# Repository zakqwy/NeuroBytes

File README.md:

## NOTE
This repository is no longer actively maintained or current. This clean break helped us do many things, such as:
- switch microcontroller platforms from ATtiny88 (8-bit AVR) to STM32L0s (ARM Cortex M0+)
- move from a single-board-fits-all strategy to specific boards that represent different types of biological elements
- change signaling from a simple 200ms pulse to a flexible mesh networking protocol
The new repositories can be found under the NeuroTinker GitHub account, found here: https://github.com/neurotinker.
# NeuroBytes
Official repo for NeuroBytes, an open-source hardware neuron simulator created by NeuroTinker, LLC. An exhuastive history of the project can be found at https://hackaday.io/project/3339-neurobytes, while more information on the company and people behind the project can be found at https://www.neurotinker.com. A good source for up-to-date and interesting pictures are the various NeuroTinker social media accounts: https://www.instagram.com/neurotinker, https://www.twitter.com/neurotinker, and https://www.facebook.com/neurotinker.
## Background
NeuroBytes were created to bridge the gap between middle- and high-school biology classes and postsecondary neuroscience education. We believe that a hands-on, modular, free-form tool in the spirit of LEGO, littleBits, or SnapCircuits that uniquely focuses on core neuroscience principles can connect engineering and biology concepts and ultimately improve STEM/STEAM retention rates for students as they pursue higher education. Our company's history goes back to 2012 and work done independently by Andrew Salveson (an architect) and Joe Burdo (a neuroscientist). After Zach Fredin created the first few generations of hardware simulators in 2014, Joe and Zach found each other via Hackaday.io and decided to collaborate on the project. In 2016, we were awarded a Phase I SBIR grant from the National Science Foundation and continue to work full-time on the project. NeuroBytes are not yet available for commercial sale, but we have sold a number of prototype kits to educators and students at a wide variety of levels and are always interested in collaborations. The project's creators can be easily reached via email: joe[at]neurotinker[dot]com and zach[at]neurotinker[dot]com.
## Hardware
All hardware files can be found under the /HARDWARE folder in this repository. The NeuroBytes boards, currently in version 0.91, were designed in KiCad v4.x. Various custom schematic symbols and PCB footprints were used, which are included in ZF.lib. The board outline itself along with the copper layer NeuroTinker logo were modified and redied for KiCad use using Inkscape and Gimp; various files titled v091-logo.xxx and v091_outline.xxx are included in the repo and were used in this process. Note that the NeuroTinker logo is a registered trademark of NeuroTinker, LLC and cannot be used without explicit permission from the company. Having said that, we urge interested parties to build and commercially sell electronic neuron simulators and accessories based on the NeuroBytes platform, keeping in mind the requirements outlined under our chosen license (GPLv3).

## Firmware
All firmware files can be found under the /FIRMWARE folder in this repository. NeuroBytes (at least v0.91) are based around the ATtiny88 platform and programmed in AVR-C using the avrdude/gcc toolchain and an Adafruit USBtinyISP programmer. Each runtime program is standalone in its folder, including a suitable Makefile that configures the proper microcontroller fuses. As expected, the test_LED program just lights the RGB LED white to test a few connections; the v091_run-iaf (stands for "integrate-and-fire") folder holds the latest firmware iteration, and includes an operating mode for direct servo control (hold the 'mode' switch down for a few seconds to change this). As with any pre-commercial work-in-progress, the firmware will be changing rapidly but any code in this repo has been thoroughly tested (so let us know if it doesn't work).

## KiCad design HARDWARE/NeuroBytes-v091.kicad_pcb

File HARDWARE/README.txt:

Copyright 2016 by Zach Fredin, NeuroTinker LLC
5/15/2016

NeuroBytes v0.9 is the ninth hardware iteration of the NeuroBytes project, a product designed and manufactured by NeuroTinker, LLC. The project is released under the terms of the GNU General Public License version 3 (LICENSE.txt). These boards are still to be considered prototypes, and as such may have bugs and mistakes that have not yet been recognized or fixed.

Changes vs NeuroBytes v0.8:

- Added on-board potentiometer
- Both axon signals now route to hardware PWM-capable pins
- Added on-board LDO and associated capacitors
- Added Schottky diode on microcontroller voltage rail
- Added OSHW logo to silkscreen
- Reduced LED hole size slightly
- Added pogo pads for testing axons, dendrites, etc.
- Changed MODE switch to standard type (vs right-angle)
- General silkscreen improvements/simplifications

Note that the PCB design file includes three copies of the board, along with a pogo rig breakout and a few accessory boards.

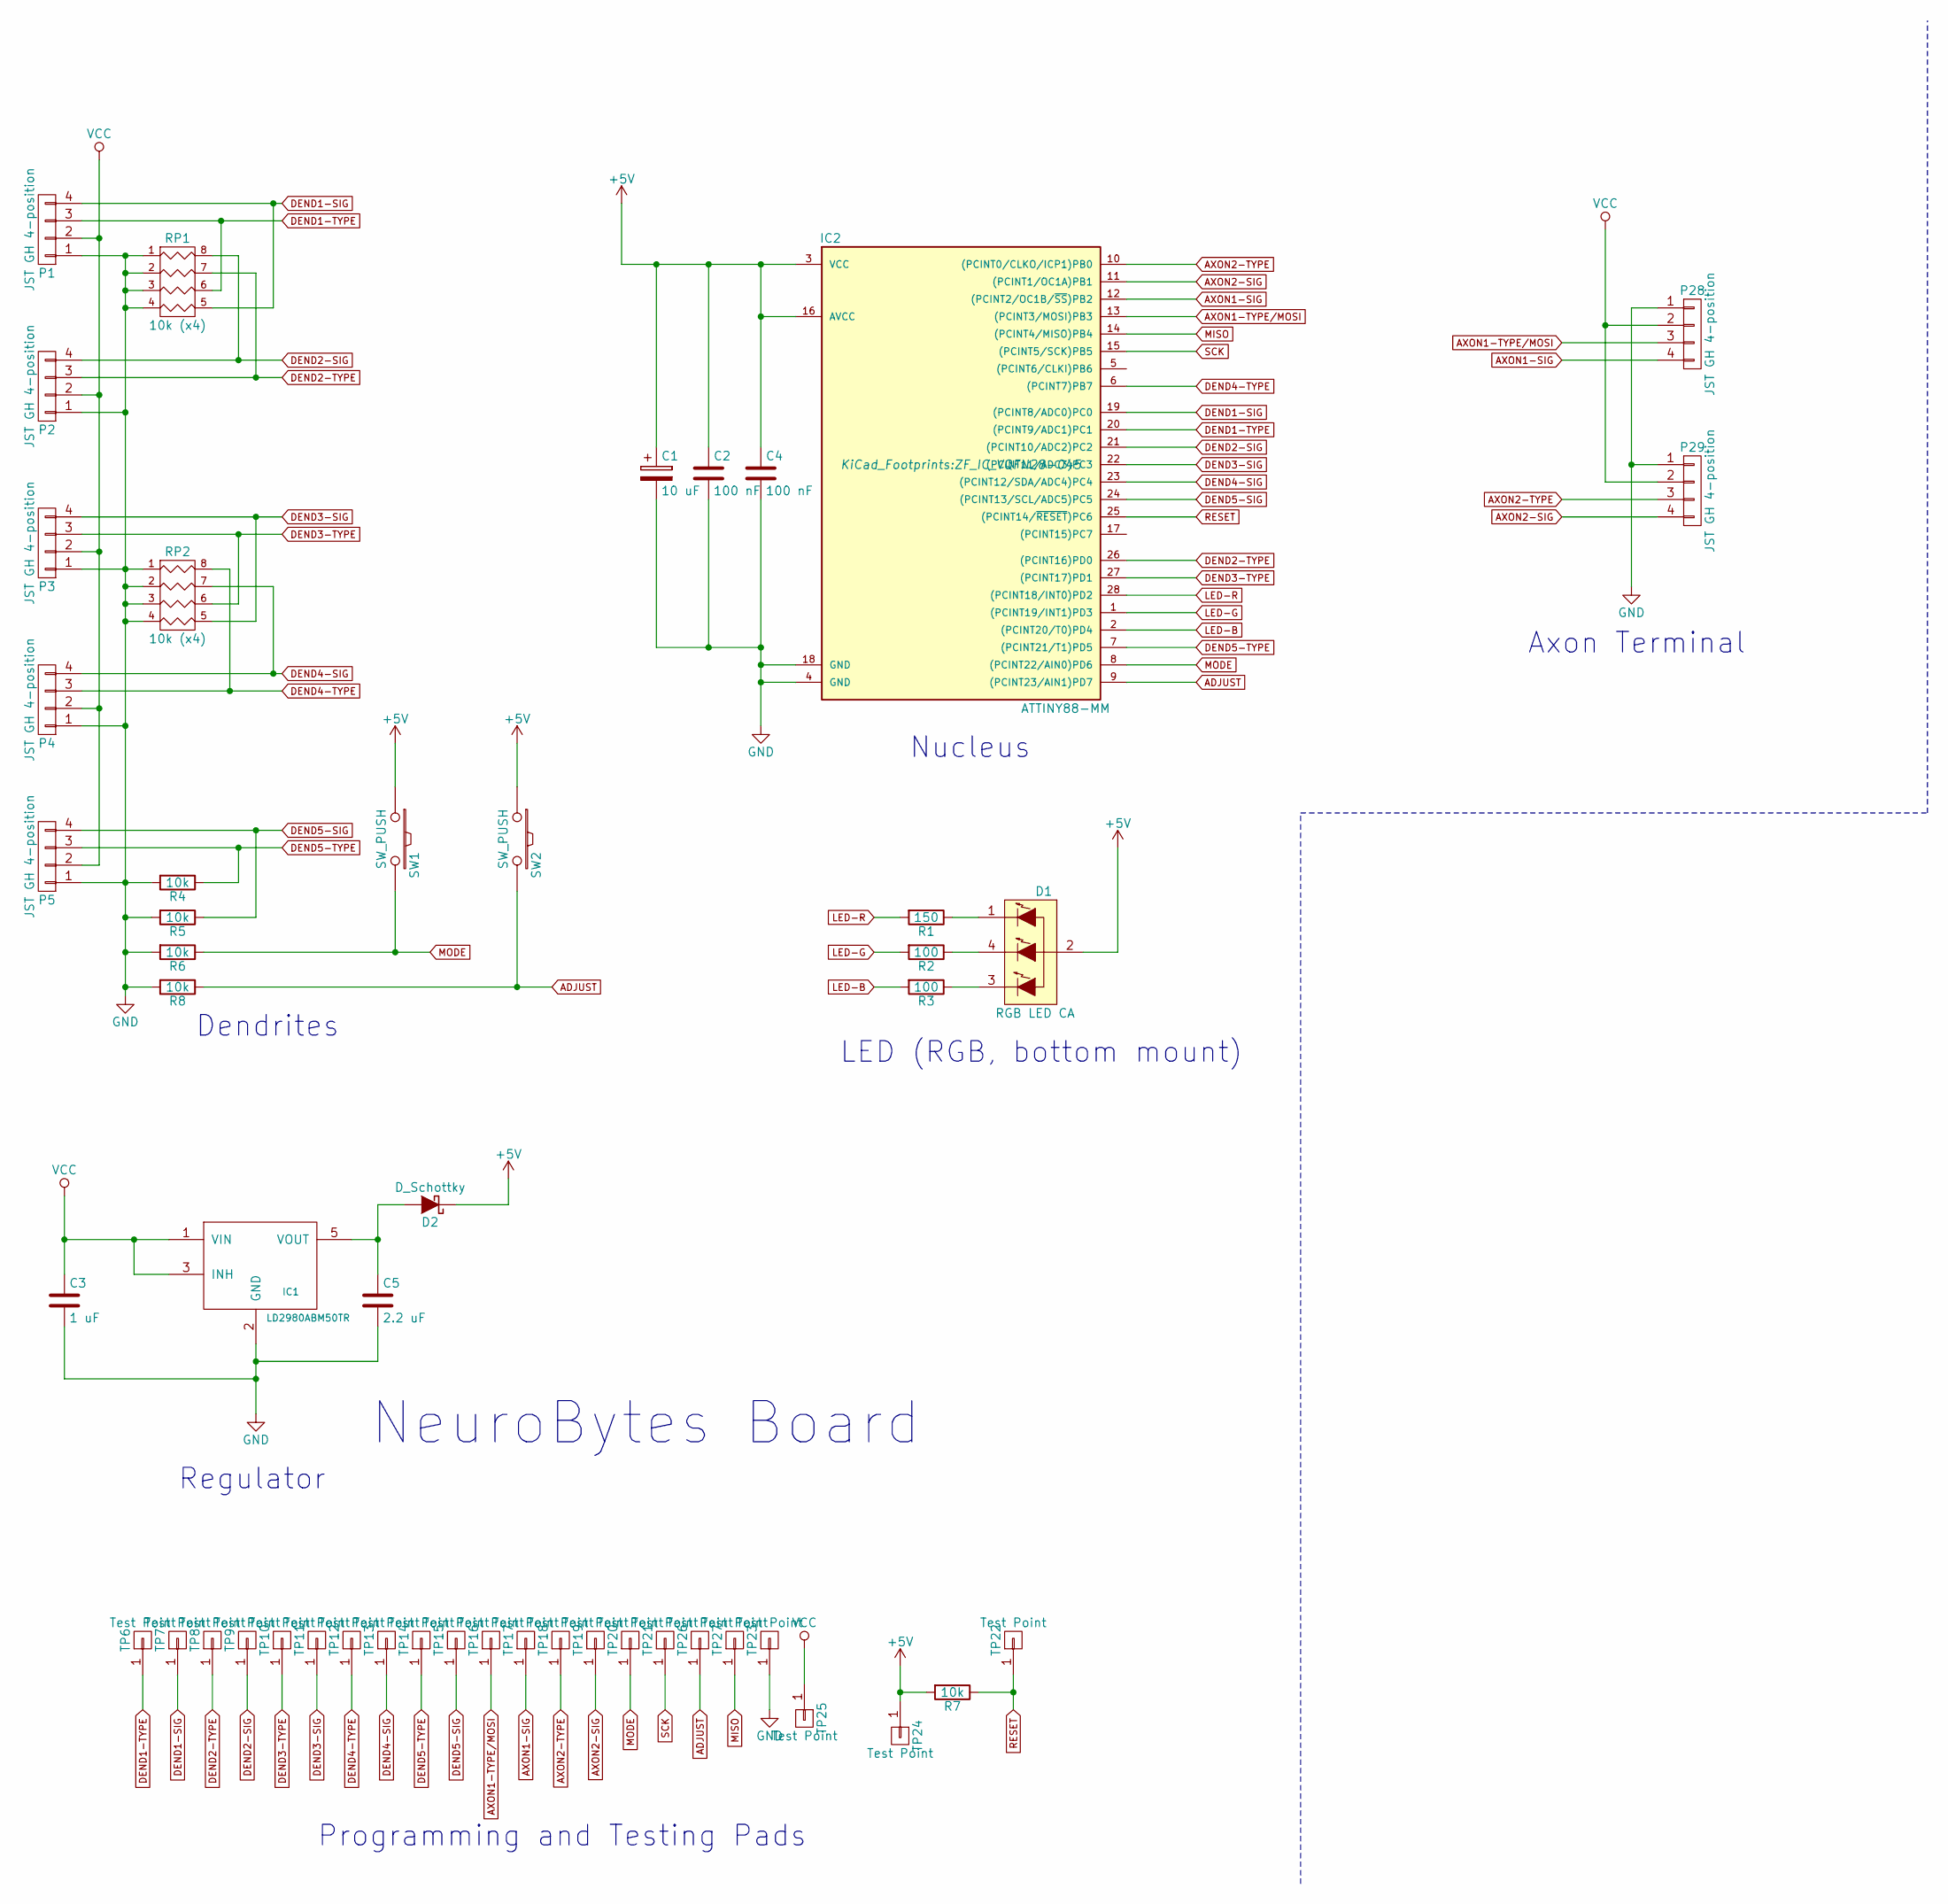
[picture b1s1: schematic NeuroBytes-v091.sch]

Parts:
C1: 10 uF; ZF_SMD_pol_1206; Mfr Part # T491A106K010AT
C2, C4: 100 nF; ZF_SMD_NonPol_0402; Mfr Part # LMK105BJ104KV-F
C3: 1 uF; ZF_SMD_NonPol_0603; Mfr Part # LMK107B7105KA-T
C5: 2.2 uF; ZF_SMD_NonPol_0603; Mfr Part # LMK107BJ225KA-T
D1: RGB LED CA; ZF_LED_RGB_SunLED_XZMDKCBDDG45S-9; Mfr Part # XZMDKCBDDG45S-9
D2: D_Schottky; ZF_SMD_pol_SC79; Mfr Part # DB2S30800L
IC1: LD2980ABM50TR; ZF_SOT23-5L; Mfr Part # LD2980ABM50TR
IC2: ATTINY88-MM; ZF_IC_VQFN28-045; Mfr Part # ATTINY88-MMHR
P1, P2, P3, P4, P5, P28, P29: JST GH 4-position; ZF_CONN_JST_GH; Mfr Part # SM04B-GHS-TB(LF)(SN)-
R1: 150; ZF_SMD_NonPol_0402; Mfr Part # RC0402FR-07150RL
R2, R3: 100; ZF_SMD_NonPol_0402; Mfr Part # RC0402FR-07100RP
R4, R5, R6, R7, R8: 10k; ZF_SMD_NonPol_0402; Mfr Part # RC0402FR-0710KL
RP1, RP2: 10k (x4); ZF_RN_4iso_CTS-0804; Mfr Part # 741C083103JP
SW1, SW2: SW_PUSH; ZF_SW_Momentary_KSEM31J; Mfr Part # KSEM31J LFS
TP6, TP7, TP8, TP9, TP10, TP11, TP12, TP13, TP14, TP15, TP16, TP17, TP18, TP19, TP20, TP21, TP22, TP23, TP24, TP25, TP26, TP27: Test Point; ZF_CONN_1-2_pad

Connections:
+5V: C1.1, C2.1, C4.1, D1.2 (COMMON_ANODE), D2.1 (K), IC2.3 (VCC), IC2.16 (AVCC), R7.2, SW1.1, SW2.1, TP24.1
ADJUST: IC2.9 ((PCINT23/AIN1)PD7), R8.1, SW2.2, TP26.1
AXON1-SIG: IC2.12 ((PCINT2/OC1B/~SS~)PB2), P28.4, TP17.1
AXON1-TYPE/MOSI: IC2.13 ((PCINT3/MOSI)PB3), P28.3, TP16.1
AXON2-SIG: IC2.11 ((PCINT1/OC1A)PB1), P29.4, TP19.1
AXON2-TYPE: IC2.10 ((PCINT0/CLKO/ICP1)PB0), P29.3, TP18.1
DEND1-SIG: IC2.19 ((PCINT8/ADC0)PC0), P1.4, RP1.5 (R4), TP7.1
DEND1-TYPE: IC2.20 ((PCINT9/ADC1)PC1), P1.3, RP1.6 (R3), TP6.1
DEND2-SIG: IC2.21 ((PCINT10/ADC2)PC2), P2.4, RP1.8 (R1), TP9.1
DEND2-TYPE: IC2.26 ((PCINT16)PD0), P2.3, RP1.7 (R2), TP8.1
DEND3-SIG: IC2.22 ((PCINT11/ADC3)PC3), P3.4, RP2.5 (R4), TP11.1
DEND3-TYPE: IC2.27 ((PCINT17)PD1), P3.3, RP2.6 (R3), TP10.1
DEND4-SIG: IC2.23 ((PCINT12/SDA/ADC4)PC4), P4.4, RP2.7 (R2), TP13.1
DEND4-TYPE: IC2.6 ((PCINT7)PB7), P4.3, RP2.8 (R1), TP12.1
DEND5-SIG: IC2.24 ((PCINT13/SCL/ADC5)PC5), P5.4, R5.1, TP15.1
DEND5-TYPE: IC2.7 ((PCINT21/T1)PD5), P5.3, R4.1, TP14.1
GND: C1.2, C2.2, C3.2, C4.2, C5.2, IC1.2 (GND), IC2.4 (GND), IC2.18 (GND), P1.1, P2.1, P3.1, P4.1, P5.1, P28.1, P29.1, R4.2, R5.2, R6.2, R8.2, RP1.1, RP1.2, RP1.3, RP1.4, RP2.1, RP2.2, RP2.3, RP2.4, TP23.1
LED-B: IC2.2 ((PCINT20/T0)PD4), R3.2
LED-G: IC2.1 ((PCINT19/INT1)PD3), R2.2
LED-R: IC2.28 ((PCINT18/INT0)PD2), R1.2
MISO: IC2.14 ((PCINT4/MISO)PB4), TP27.1
MODE: IC2.8 ((PCINT22/AIN0)PD6), R6.1, SW1.2, TP20.1
unnamed: C5.1, D2.2 (A), IC1.5 (VOUT)
unnamed: D1.1 (RED_CATHODE), R1.1
unnamed: D1.3 (BLUE_CATHODE), R3.1
unnamed: D1.4 (GREEN_CATHODE), R2.1
RESET: IC2.25 ((PCINT14/~RESET~)PC6), R7.1, TP22.1
SCK: IC2.15 ((PCINT5/SCK)PB5), TP21.1
VCC: C3.1, IC1.1 (VIN), IC1.3 (INH), P1.2, P2.2, P3.2, P4.2, P5.2, P28.2, P29.2, TP25.1

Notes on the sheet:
Nucleus
Dendrites
Regulator
LED (RGB, bottom mount)
Axon Terminal
Programming and Testing Pads
NeuroBytes Board

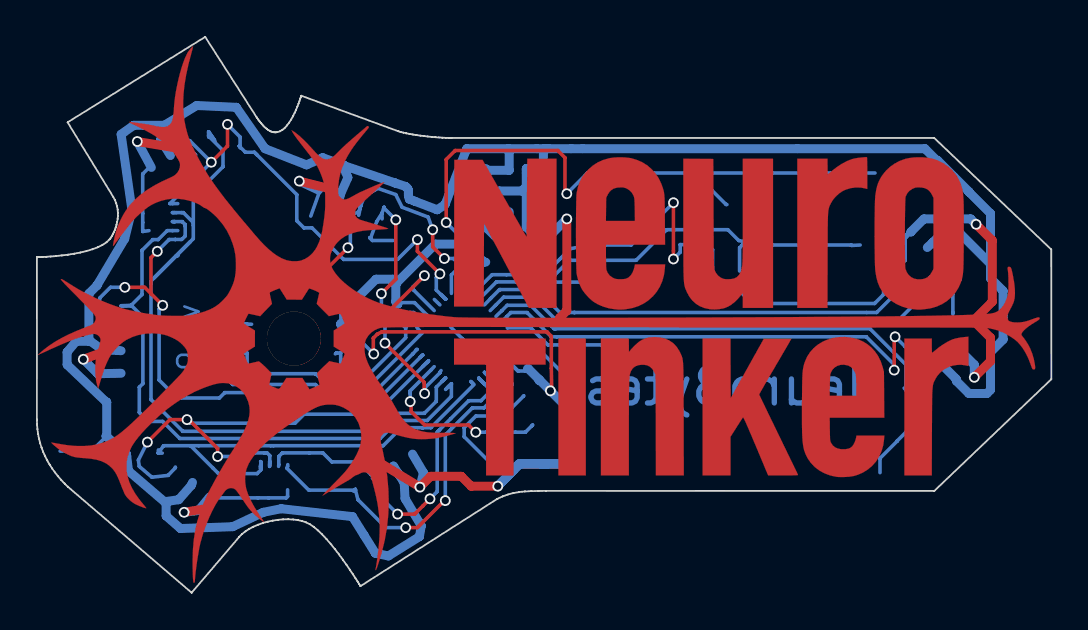
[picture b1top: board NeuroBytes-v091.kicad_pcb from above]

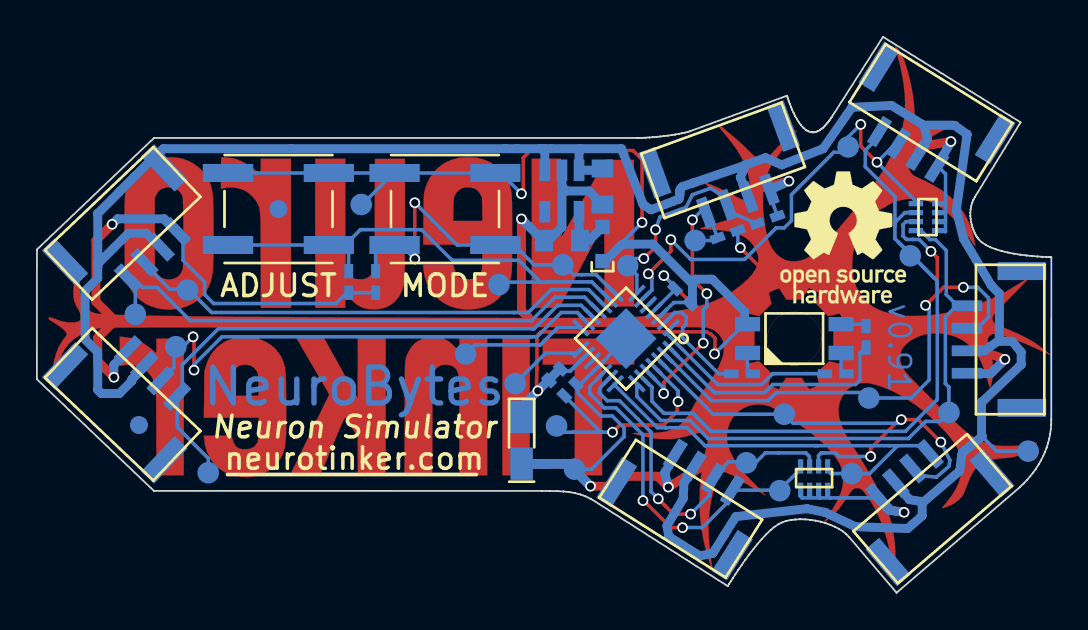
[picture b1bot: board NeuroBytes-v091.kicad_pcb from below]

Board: 2 copper layers, 56.4 x 30.9 mm, 50 parts (50 on the bottom side), 29 nets.

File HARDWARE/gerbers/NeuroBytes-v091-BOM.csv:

Title,
Revision,
Date,
Generated,Thu 16 Jun 2016 06:22:55 PM CDT
Company,
Comment 1,
Comment 2,
Comment 3,
Comment 4,
Total Parts,50
Total Unique Parts,15



Ref,Qty,Value,Link,Mfr,Mfr Part #,Package,RoHS,Subs Allowed,
C4 C2 ,2,100 nF,https://www.digikey.com/product-detail/en/taiyo-yuden/LMK105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,Taiyo Yuden,LMK105BJ104KV-F,0402,Yes,Yes
C3 ,1,1 uF,https://www.digikey.com/product-detail/en/taiyo-yuden/LMK107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,Taiyo Yuden,LMK107B7105KA-T,0603,Yes,Yes
C5 ,1,2.2 uF,https://www.digikey.com/product-detail/en/taiyo-yuden/LMK107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,Taiyo Yuden,LMK107BJ225KA-T,0603,Yes,Yes
C1 ,1,10 uF,https://www.digikey.com/product-detail/en/kemet/T491A106K010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,Kemet,T491A106K010AT,1206,Yes,Yes
D1 ,1,RGB LED CA,https://www.digikey.com/product-detail/en/sunled/XZMDKCBDDG4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,SunLED,XZMDKCBDDG45S-9,4-PLCC  bottom mtg,Yes,No
D2 ,1,D_Schottky,https://www.digikey.com/product-detail/en/panasonic-electron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,Panasonic Electric Components,DB2S30800L,SC-79,Yes,Yes
IC2 ,1,ATTINY88-MM,https://www.digikey.com/product-search/en?keywords=ATTINY88-MMHR-ND,Atmel,ATTINY88-MMHR,28-VQFN (4x4),Yes,No
IC1 ,1,LD2980ABM50TR,https://www.digikey.com/product-detail/en/stmicroelectronics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,STMicroelectronics,LD2980ABM50TR,SOT-23-5,Yes,No
P1 P2 P3 P4 P5 P28 P29 ,7,JST GH 4-position,https://www.digikey.com/product-detail/en/jst-sales-america-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,JST,SM04B-GHS-TB(LF)(SN)-,JST GH,Yes,No
R1 ,1,150,https://www.digikey.com/product-detail/en/yageo/RC0402FR-071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,Yageo,RC0402FR-07150RL,0402,Yes,Yes
R2 R3 ,2,100,https://www.digikey.com/product-detail/en/yageo/RC0402FR-071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,Yageo,RC0402FR-07100RP,0402,Yes,Yes
R4 R5 R6 R7 R8 ,5,10k,https://www.digikey.com/product-detail/en/yageo/RC0402FR-071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,Yageo,RC0402FR-0710KL,0402,Yes,Yes
RP1 RP2 ,2,10k (x4),https://www.digikey.com/product-detail/en/cts-resistor-produ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,CTS Resistor Products,741C083103JP,0804,Yes,Yes
SW1 SW2 ,2,SW_PUSH,https://www.digikey.com/product-detail/en/c-k-components/KSE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,C&K Components,KSEM31J LFS,J Lead,Yes,No
TP24 TP21 TP22 TP23 TP6 TP7 TP8 TP9 TP10 TP11 TP12 TP13 TP14 TP15 TP16 TP17 TP18 TP19 TP25 TP20 TP26 TP27 ,22,Test Point, , , , , , 




BOM made with KICAD_BOM_WIZARD (https://github.com/HashDefineElectronics/KiCad_BOM_Wizard.git)
Generated Thu 16 Jun 2016 06:22:55 PM CDT

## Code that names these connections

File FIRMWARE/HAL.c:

#include <avr/io.h>
#include <avr/interrupt.h>
#include <avr/pgmspace.h>
#include "HAL.h"
#include "bit_ops.h"
#include "neuron.h"

volatile unsigned char ms_tick;
static unsigned char timer_tick = 0;


void systemInit(void)
{
	// TODO: use bit ops here
	/* set up LED */
	DDRD |= ((1<<PD2) | (1<<PD3) | (1<<PD4));
	PORTD |= ((1<<PD2) | (1<<PD3) | (1<<PD4)); //set pins = LED off

	/* set up dendrites */
	DDRC &= ~((1<<PC0) | (1<<PC1) | (1<<PC2) | (1<<PC3) | (1<<PC4) | (1<<PC5));
	DDRD &= ~((1<<PD0) | (1<<PD1) | (1<<PD5));
	DDRB &= ~(1<<PB7);

	/* set up axons */
	DDRB |= ((1<<PB0) | (1<<PB1) | (1<<PB2) | (1<<PB3));
	//PORTB &= ~((1<<PB0) | (1<<PB1) | (1<<PB2) | (1<<PB3));

	/* set up mode switch */
	DDRD &= ~(1<<PD6);

	/* set up adjust switch */
	DDRD &= ~(1<<PD7);


	// set up timer/counter1: OC1B is PB2
	TCCR1A |= ((1<<COM1A1) | (1<<COM1B1)); //Fast PWM mode: clear OC1B on Compare Match, set at TOP
	TCCR1A |= ((1<<WGM10) | (1<<WGM11)); //Fast PWM, 10-bit

	OCR1BL = 48; //servo range: 32 (1ms) - 63 (2ms)

	// set up SPI in slave mode
	/*
	DDRB = (1<<PB5);
	SPCR = (1<<SPE);
	
	bit_clear(PRR, BIT(2)); // tell the power reduction register not to turn off SPI
	*/
}

void setupTimer(void)
{
	// write timer registers
	// set timer to interrupt at 20 kHz
	
	TCCR0A = 0x0A;	//  Set CTC0, and CS01 for clear timer on compare mode
	//	and divide by 8 prescaler
	TIMSK0 = 0x02;	//	Set OCIE0A to enable Compare A interrupt
	TIMSK1 = 0;
	OCR0A  = 49;	//	Set Compare A register for 49 so interrupt triggers
	//  every 50 ticks of prescaled clock
	
	//test these:
	sei(); // enable interrupts
}

unsigned char readDendritePin(unsigned char pin_number, dendrite_types dendrite_type)
{
	switch(pin_number) {
		case 0:
		switch(dendrite_type) {
			case EXCITATORY:
				return bit_get(PINC,BIT0_MASK) ? 1 : 0;
			case INHIBITORY:
				return bit_get(PINC,BIT1_MASK) ? 1 : 0;
		}
		case 1:
		switch(dendrite_type) {
			case EXCITATORY:
				return bit_get(PINC,BIT2_MASK) ? 1 : 0;
			case INHIBITORY:
				return bit_get(PIND,BIT0_MASK) ? 1 : 0;
		}
		case 2:
		switch(dendrite_type) {
			case EXCITATORY:
				return bit_get(PINC,BIT3_MASK) ? 1 : 0;
			case INHIBITORY:
				return bit_get(PIND,BIT1_MASK) ? 1 : 0;
		}
		case 3:
		switch(dendrite_type) {
			case EXCITATORY:
				return bit_get(PINC,BIT4_MASK) ? 1 : 0;
			case INHIBITORY:
				return bit_get(PINB,BIT7_MASK) ? 1 : 0;
		}
		case 4:
		switch(dendrite_type) {
			case EXCITATORY:
				return bit_get(PINC,BIT5_MASK) ? 1 : 0;
			case INHIBITORY:
				return bit_get(PIND,BIT5_MASK) ? 1 : 0;
		}
	}
	return 0;
}

static inline void timeInterruptRoutine(void)
{	
	if(++timer_tick > 20) { 
		timer_tick = 0;
		ms_tick = 1;
	}
	updateLED();
}

inline void setOutputPin(unsigned char pin_number)
{
	/*
		TODO: separate this into setAxonPin(axon_num) and setLED(led_color)

		this is a super dumb abstraction right now with a pin_number lookup table
	*/
	switch(pin_number) {
		case 0:
		bit_set(PORTD,BIT2_MASK);
		break;
		case 1:
		bit_set(PORTD,BIT3_MASK);
		break;
		case 2:
		bit_set(PORTD,BIT4_MASK);
		break;
		case 3:
		bit_set(PORTB,BIT3_MASK);
		break;
		case 4:
		bit_set(PORTB,BIT2_MASK);
		bit_set(PORTB,BIT3_MASK);
		break;
		case 5:
		bit_set(PORTB,BIT1_MASK);
		break;
		case 6:
		bit_set(PORTB,BIT1_MASK);
		bit_set(PORTB,BIT0_MASK);
		break;
		default:
		break;
	}
}

inline void clearOutputPin(unsigned char pin_number)
{
	/*
		TODO: separate this into clearAxonPin(axon_num) and clearLED(led_color)

		this is a super dumb abstraction right now with a pin_number lookup table
	*/
	switch(pin_number) {
		case 0:
		bit_clear(PORTD,BIT2_MASK);
		break;
		case 1:
		bit_clear(PORTD,BIT3_MASK);
		break;
		case 2:
		bit_clear(PORTD,BIT4_MASK);
		break;
		case 4:
		bit_clear(PORTB,BIT2_MASK);
		bit_clear(PORTB,BIT3_MASK);
		break;
		case 6:
		bit_clear(PORTB,BIT1_MASK);
		bit_clear(PORTB,BIT0_MASK);
		break;
		default:
		break;
	}
}

char SPI_Receive(void)
{
/*
	if (SPSR & (1<<SPIF)) {
		return SPDR;
	}
	*/
	return 0;
}

ISR(TIMER0_COMPA_vect)
{
	timeInterruptRoutine();
}

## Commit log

2016-09-09 added a few picures (along with pictures folder)
2016-09-09 aded picture to readme (or at least tried to?)
2016-09-09 pictures in readme, attempt 2 (or 3?)
2016-09-09 added PCB and schematic screenshots
2016-11-14 Updated getDendriteType() for compatibility with switches that only hold the TYPE line high when actuated.
2017-08-17 updated coefficients to allow 4-NB loop (CW only). added bit_ops.h file. changed back to green-at-rest indication.
2018-08-03 Updated README.md to include link to new repos.
